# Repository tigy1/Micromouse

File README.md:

# Micromouse
hto's micromouse personal project

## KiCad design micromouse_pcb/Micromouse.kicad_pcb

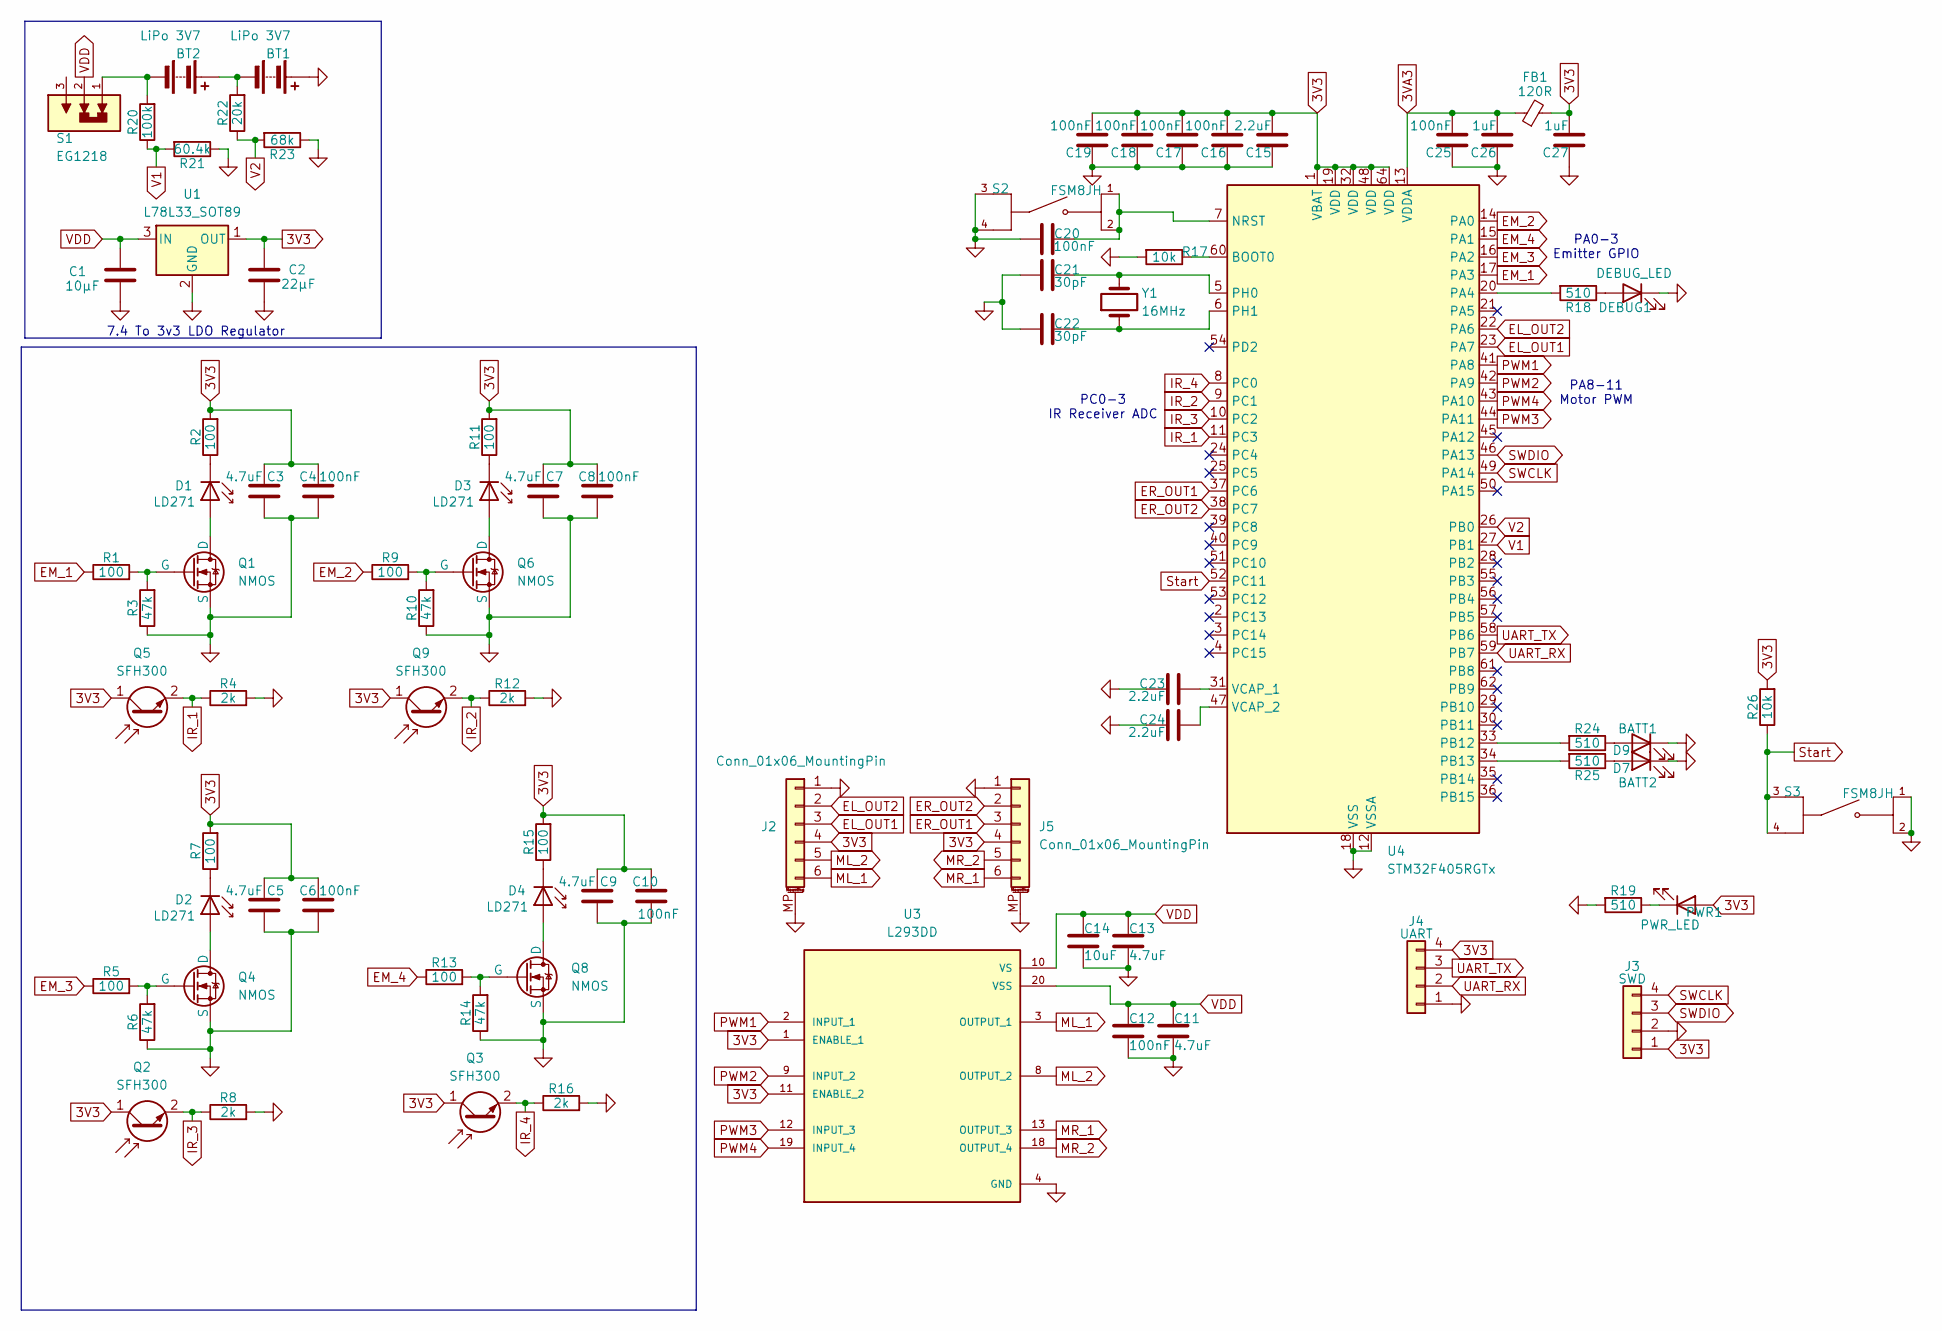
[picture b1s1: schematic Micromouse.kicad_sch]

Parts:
BT1, BT2: LiPo 3V7; JST_PH_B2B-PH-K_1x02_P2.00mm_Vertical
C1: 10μF; C_0805_2012Metric
C2: 22μF; C_0805_2012Metric
C3, C5, C7, C9, C11, C13: 4.7uF; C_0805_2012Metric
C4, C6, C8, C10, C12, C16, C17, C18, C19, C20, C25: 100nF; C_0603_1608Metric
C14: 10uF; C_0805_2012Metric
C15, C23, C24: 2.2uF; C_0805_2012Metric
C21, C22: 30pF; C_0805_2012Metric
C26, C27: 1uF; C_0603_1608Metric
D1, D2, D3, D4: LD271; led_micro
D7: BATT2; LED_0805_2012Metric
D9: BATT1; LED_0805_2012Metric
DEBUG1: DEBUG_LED; LED_0805_2012Metric
FB1: 120R; L_0603_1608Metric
J2, J5: Conn_01x06_MountingPin; JST_SH_BM06B-SRSS-TB_1x06-1MP_P1.00mm_Vertical
J3: SWD; PinHeader_1x04_P2.54mm_Vertical
J4: UART; PinHeader_1x04_P2.54mm_Vertical
PWR1: PWR_LED; LED_0805_2012Metric
Q1, Q4, Q6, Q8: NMOS; TO-92_Inline
Q2, Q3, Q5, Q9: SFH300; led_micro
R1, R2, R5, R7, R9, R11, R13, R15: 100; R_0805_2012Metric
R3, R6, R10, R14: 47k; R_0805_2012Metric
R4, R8, R12, R16: 2k; R_0805_2012Metric
R17, R26: 10k; R_0805_2012Metric
R18, R19, R24, R25: 510; R_0805_2012Metric
R20: 100k; R_0805_2012Metric
R21: 60.4k; R_0805_2012Metric
R22: 20k; R_0805_2012Metric
R23: 68k; R_0805_2012Metric
S1: EG1218; SW_EG1218
S2, S3: FSM8JH; SW4_1825910-B_TEC; PARTREV 8-1773450-9
U1: L78L33_SOT89; SOT-89-3
U3: L293DD; SOIC127P1032X265-20N; PARTREV N/A; DigiKey_Part_Number 497-1390-5-ND
U4: STM32F405RGTx; LQFP-64_10x10mm_P0.5mm
Y1: 16MHz; Crystal_HC49-4H_Vertical

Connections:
3V3: C2.1, C3.1, C4.1, C5.1, C6.1, C7.1, C8.1, C9.1, C10.1, C15.2, C16.2, C17.2, C18.2, C19.2, C27.2, FB1.2, J2.4, J3.1, J4.4, J5.4, PWR1.2 (A), Q2.1 (C), Q3.1 (C), Q5.1 (C), Q9.1 (C), R2.2, R7.2, R11.2, R15.2, R26.2, U1.1 (OUT), U3.1 (ENABLE_1), U3.11 (ENABLE_2), U4.1 (VBAT), U4.19 (VDD), U4.32 (VDD), U4.48 (VDD), U4.64 (VDD); also elsewhere on the board
3VA3: C25.2, C26.2, FB1.1, U4.13 (VDDA)
EL_OUT1: J2.3, U4.23 (PA7)
EL_OUT2: J2.2, U4.22 (PA6)
EM_1: R1.1, U4.17 (PA3)
EM_2: R9.1, U4.14 (PA0)
EM_3: R5.1, U4.16 (PA2)
EM_4: R13.1, U4.15 (PA1)
ER_OUT1: J5.3, U4.37 (PC6)
ER_OUT2: J5.2, U4.38 (PC7)
GND: BT1.1 (+), C1.2, C2.2, C3.2, C4.2, C5.2, C6.2, C7.2, C8.2, C9.2, C10.2, C11.2, C12.2, C13.2, C14.2, C15.1, C16.1, C17.1, C18.1, C19.1, C20.2, C21.1, C22.1, C23.1, C24.1, C25.1, C26.1, C27.1, D7.1 (K), D9.1 (K), DEBUG1.1 (K), J2.1, J2.MP (MountPin), J3.2, J4.1, J5.1, J5.MP (MountPin), Q1.3 (S), Q4.3 (S), Q6.3 (S), Q8.3 (S), R3.1, R4.2, R6.1, R8.2, R10.1, R12.2, R14.1, R16.2, R17.2, R19.2, R21.1, R23.1, S2.3, S2.4, S3.1, S3.2, U1.2 (GND), U3.4 (GND), U3.5 (GND), U3.6 (GND), U3.7 (GND), U3.14 (GND), U3.15 (GND), U3.16 (GND), U3.17 (GND), U4.12 (VSSA), U4.18 (VSS), U4.63 (VSS); also elsewhere on the board
IR_1: Q5.2 (E), R4.1, U4.11 (PC3)
IR_2: Q9.2 (E), R12.1, U4.9 (PC1)
IR_3: Q2.2 (E), R8.1, U4.10 (PC2)
IR_4: Q3.2 (E), R16.1, U4.8 (PC0)
ML_1: J2.6, U3.3 (OUTPUT_1)
ML_2: J2.5, U3.8 (OUTPUT_2)
MR_1: J5.6, U3.13 (OUTPUT_3)
MR_2: J5.5, U3.18 (OUTPUT_4)
unnamed: BT1.2 (-), BT2.1 (+), R22.2
unnamed: BT2.2 (-), R20.2, S1.1
unnamed: D1.2 (A), Q1.1 (D)
unnamed: D1.1 (K), R2.1
unnamed: D2.2 (A), Q4.1 (D)
unnamed: D2.1 (K), R7.1
unnamed: D3.2 (A), Q6.1 (D)
unnamed: D3.1 (K), R11.1
unnamed: D4.2 (A), Q8.1 (D)
unnamed: D4.1 (K), R15.1
unnamed: D7.2 (A), R25.1
unnamed: D9.2 (A), R24.1
unnamed: DEBUG1.2 (A), R18.1
unnamed: PWR1.1 (K), R19.1
unnamed: Q1.2 (G), R1.2, R3.2
unnamed: Q4.2 (G), R5.2, R6.2
unnamed: Q6.2 (G), R9.2, R10.2
unnamed: Q8.2 (G), R13.2, R14.2
unnamed: R17.1, U4.60 (BOOT0)
unnamed: C20.1, S2.1, S2.2, U4.7 (NRST)
unnamed: R18.2, U4.20 (PA4)
unnamed: R24.2, U4.33 (PB12)
unnamed: R25.2, U4.34 (PB13)
unnamed: C21.2, U4.5 (PH0), Y1.2
unnamed: C22.2, U4.6 (PH1), Y1.1
unnamed: C23.2, U4.31 (VCAP_1)
unnamed: C24.2, U4.47 (VCAP_2)
PWM1: U3.2 (INPUT_1), U4.41 (PA8)
PWM2: U3.9 (INPUT_2), U4.42 (PA9)
PWM3: U3.12 (INPUT_3), U4.44 (PA11)
PWM4: U3.19 (INPUT_4), U4.43 (PA10)
SWCLK: J3.4, U4.49 (PA14)
SWDIO: J3.3, U4.46 (PA13)
Start: R26.1, S3.3, S3.4, U4.52 (PC11)
UART_RX: J4.2, U4.59 (PB7)
UART_TX: J4.3, U4.58 (PB6)
V1: R20.1, R21.2, U4.27 (PB1)
V2: R22.1, R23.2, U4.26 (PB0)
VDD: C1.1, C11.1, C12.1, C13.1, C14.1, S1.2, U1.3 (IN), U3.10 (VS), U3.20 (VSS)

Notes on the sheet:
PC0-3 IR Receiver ADC
PA8-11 Motor PWM
7.4 To 3v3 LDO Regulator
PA0-3 Emitter GPIO

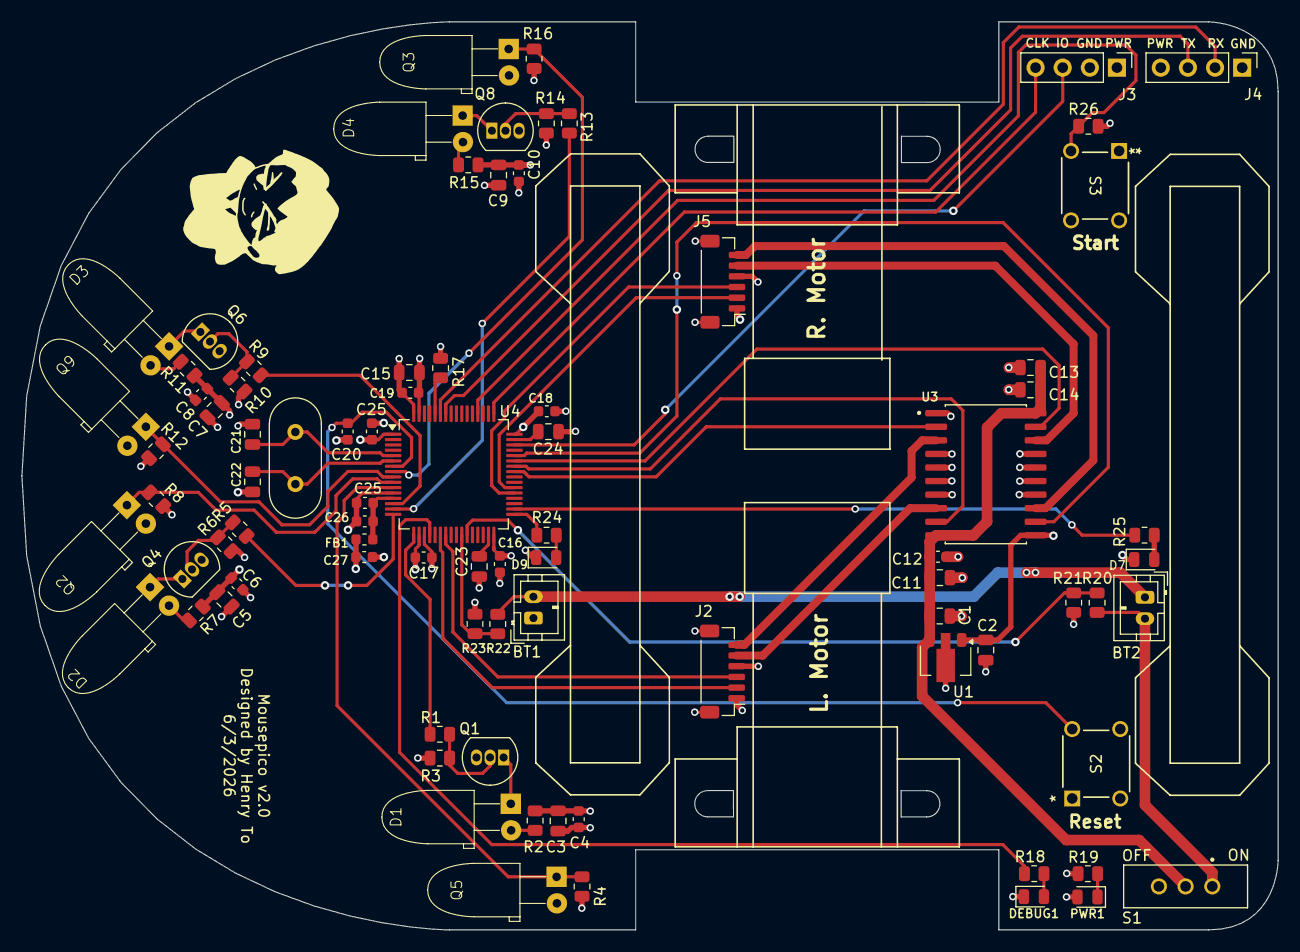
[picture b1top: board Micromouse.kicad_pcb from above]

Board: 4 copper layers, 117.6 x 85.0 mm, 84 parts (0 on the bottom side), 58 nets.

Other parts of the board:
C25#2: 100nF; C_0603_1608Metric

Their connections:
3V3: C25#2.1; also elsewhere on the board
GND: C25#2.2; also elsewhere on the board

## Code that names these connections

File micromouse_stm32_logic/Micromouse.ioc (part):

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Mcu.Name=STM32F405RGTx
Mcu.Package=LQFP64
Mcu.UserName=STM32F405RGTx
PA0-WKUP.GPIOParameters=GPIO_Label
PA0-WKUP.GPIO_Label=Front_Right_Emitter
PA0-WKUP.Signal=GPIO_Output
PA1.GPIOParameters=GPIO_Label
PA1.GPIO_Label=Right_Emitter
PA1.Signal=GPIO_Output
PA10.Signal=S_TIM1_CH3
PA11.Signal=S_TIM1_CH4
PA13.Mode=Serial_Wire
PA13.Signal=SYS_JTMS-SWDIO
PA14.Mode=Serial_Wire
PA14.Signal=SYS_JTCK-SWCLK
PA2.GPIOParameters=GPIO_Label
PA2.GPIO_Label=Front_Left_Emitter
PA2.Signal=GPIO_Output
PA3.GPIOParameters=GPIO_Label
PA3.GPIO_Label=Left_Emitter
PA3.Signal=GPIO_Output
PA6.GPIOParameters=GPIO_Label
PA6.GPIO_Label=LeftEncoderCh1
PA6.Signal=S_TIM3_CH1
PA7.GPIOParameters=GPIO_Label
PA7.GPIO_Label=LeftEncoderCh2
PA7.Signal=S_TIM3_CH2
PA8.Signal=S_TIM1_CH1
PA9.Signal=S_TIM1_CH2
PB0.Signal=SharedAnalog_PB0
PB1.Signal=SharedAnalog_PB1
PB10.Mode=Asynchronous
PB10.Signal=USART3_TX
PB11.Mode=Asynchronous
PB11.Signal=USART3_RX
PC0.GPIOParameters=GPIO_Label
PC0.GPIO_Label=Right_Receiver
PC0.Signal=SharedAnalog_PC0
PC1.GPIOParameters=GPIO_Label
PC1.GPIO_Label=Front_Right_Receiver
PC1.Signal=SharedAnalog_PC1
PC11.GPIOParameters=GPIO_Label,GPIO_ModeDefaultEXTI
PC11.GPIO_Label=START_BUTTON
PC11.GPIO_ModeDefaultEXTI=GPIO_MODE_IT_RISING_FALLING
PC11.Signal=GPXTI11
PC13-ANTI_TAMP.GPIOParameters=GPIO_Label
PC13-ANTI_TAMP.GPIO_Label=DEBUG_LED
PC13-ANTI_TAMP.Signal=GPIO_Output
PC2.GPIOParameters=GPIO_Label
PC2.GPIO_Label=Front_Left_Receiver
PC2.Signal=SharedAnalog_PC2
PC3.GPIOParameters=GPIO_Label
PC3.GPIO_Label=Left_Receiver
PC3.Signal=SharedAnalog_PC3
PC6.GPIOParameters=GPIO_Label
PC6.GPIO_Label=RightEncoderCh2
PC6.Signal=S_TIM8_CH1
PC7.GPIOParameters=GPIO_Label
PC7.GPIO_Label=RightEncoderCh1
PC7.Signal=S_TIM8_CH2
PC8.GPIOParameters=GPIO_Label
PC8.GPIO_Label=L_BATT_LED
PC8.Signal=GPIO_Output
PC9.GPIOParameters=GPIO_Label
PC9.GPIO_Label=R_BATT_LED
PC9.Signal=GPIO_Output
PH0-OSC_IN.Mode=HSE-External-Oscillator
PH0-OSC_IN.Signal=RCC_OSC_IN
PH1-OSC_OUT.Mode=HSE-External-Oscillator
PH1-OSC_OUT.Signal=RCC_OSC_OUT
RCC.HSE_VALUE=16000000
RCC.SYSCLKFreq_VALUE=72000000
RCC.SYSCLKSource=RCC_SYSCLKSOURCE_PLLCLK
board=custom

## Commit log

2026-05-22 Created .gitignore for stm32cubeide
2026-05-22 Updated .gitignore
    changed to only including the ones i want instead of excluding everything else
2026-05-22 Added stm32 & kicad files
2026-05-22 Update .gitignore
    allowed stm32 folder traversal
2026-05-22 testing
2026-05-22 testing pt2
2026-05-22 fixed ignore again by allowing repo files
2026-05-22 prob final gitignore fix
2026-05-31 v2 kicad micromouse started, and turning is now possible but please fix distance reading and distance pids
2026-06-04 finished v2 micromouse, finished move function, todo: fix distance pid
2026-06-05 fixed wheel direction encoder readings (forward = +, backward = -, left = -, right = +), did some wip pid tuning
2026-06-07 Fixed turning, confirmed moving works. Started working on infared system. Notes for self: added PTFE pads for lower fricion and make sure batteries are balanced on either ends of mouse, don't have ba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
2026-06-07 finished ir sensor code, testing will follow
